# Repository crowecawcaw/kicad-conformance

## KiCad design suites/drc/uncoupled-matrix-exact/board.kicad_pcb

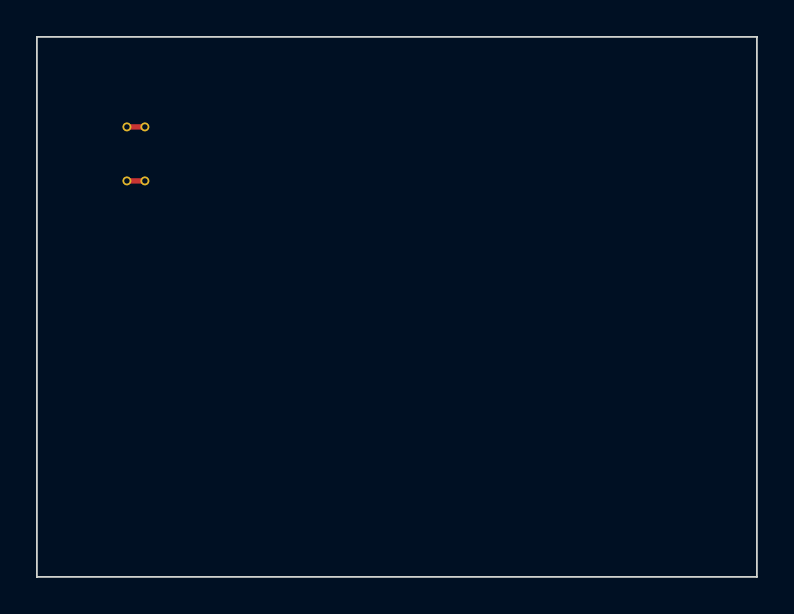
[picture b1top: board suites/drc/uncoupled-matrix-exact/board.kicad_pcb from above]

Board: 2 copper layers, 40.0 x 30.0 mm, 4 parts (0 on the bottom side), 2 nets.

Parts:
PAIR_NA: TestPad
PAIR_NB: TestPad
PAIR_PA: TestPad
PAIR_PB: TestPad

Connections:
PAIR_N: PAIR_NA.1, PAIR_NB.1
PAIR_P: PAIR_PA.1, PAIR_PB.1

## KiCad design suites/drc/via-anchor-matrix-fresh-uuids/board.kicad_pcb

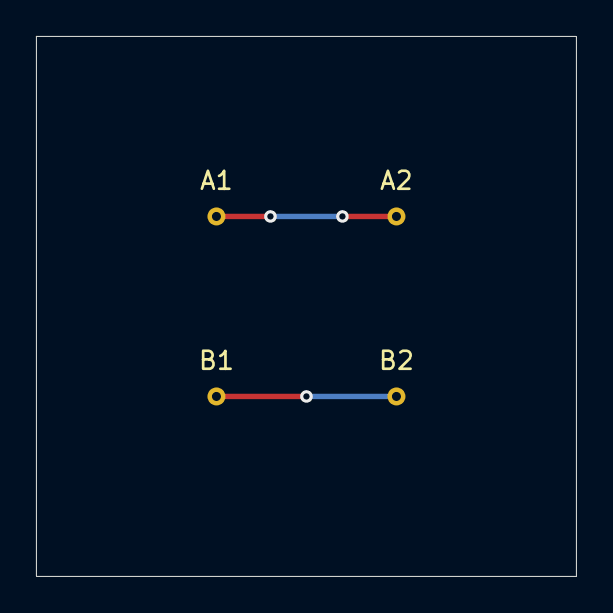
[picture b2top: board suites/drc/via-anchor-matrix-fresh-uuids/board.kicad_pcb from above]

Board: 2 copper layers, 30.0 x 30.0 mm, 4 parts (0 on the bottom side), 2 nets.

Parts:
A1, A2: P
B1, B2: P

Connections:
ONE: A1.1, A2.1
TWO: B1.1, B2.1
